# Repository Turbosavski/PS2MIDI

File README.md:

# PS2MIDI

PS/2 protocol and devices as midi interfaces: computer keyboard, mouse, touchpad

KiCad 5.1.5 files are provided for the small pcb board. For now existing / tested as a single sided prototypes for touchpad and computer keyboard. 

Previouly known as AI_SI Touchpad Piano (-> http://www.ljudmila.org/~savskib/?p=979). It is a midi trigger device based on a touchpad system found in any laptop computer – brought to a form of an oversimplified instrument that acts as (ahm...) piano. This module (-> https://www.serdashop.com/waveblaster) replaces the first version with Yamaha XG Midi daughter board (the 90s). My basic interest was just piano sounds.

The heart of the system is (of course) arduino. Arduino Promicro can be set as native usb device – so it was chosen (Sparkfun Pro micro 5V 16MHz version – a Chinese clone). An old laptop (sony vaio) provided a touchpad and parts to make the instrument housing. 

After the touchpad version an old ps/2 computer keyboard was used to some extent with adaptations to the relevant arduino library. Another option is of course the mouse - this would be probably very similar to touchpad. 

All these arduino sketches are available here in their latest development versions:
-> keyboardProMicro04
-> touchPadProMicro14

Quite some work was done in 2019 with adding the AI part on the level of three arduino libraries: midimelodics, midirhythmics and midistatistics - not yet finished but soon to be uploaded. Similar work is lately been done as a flute-like breath controller - but without the midi-synth.

Available here - in case the virus gets me...

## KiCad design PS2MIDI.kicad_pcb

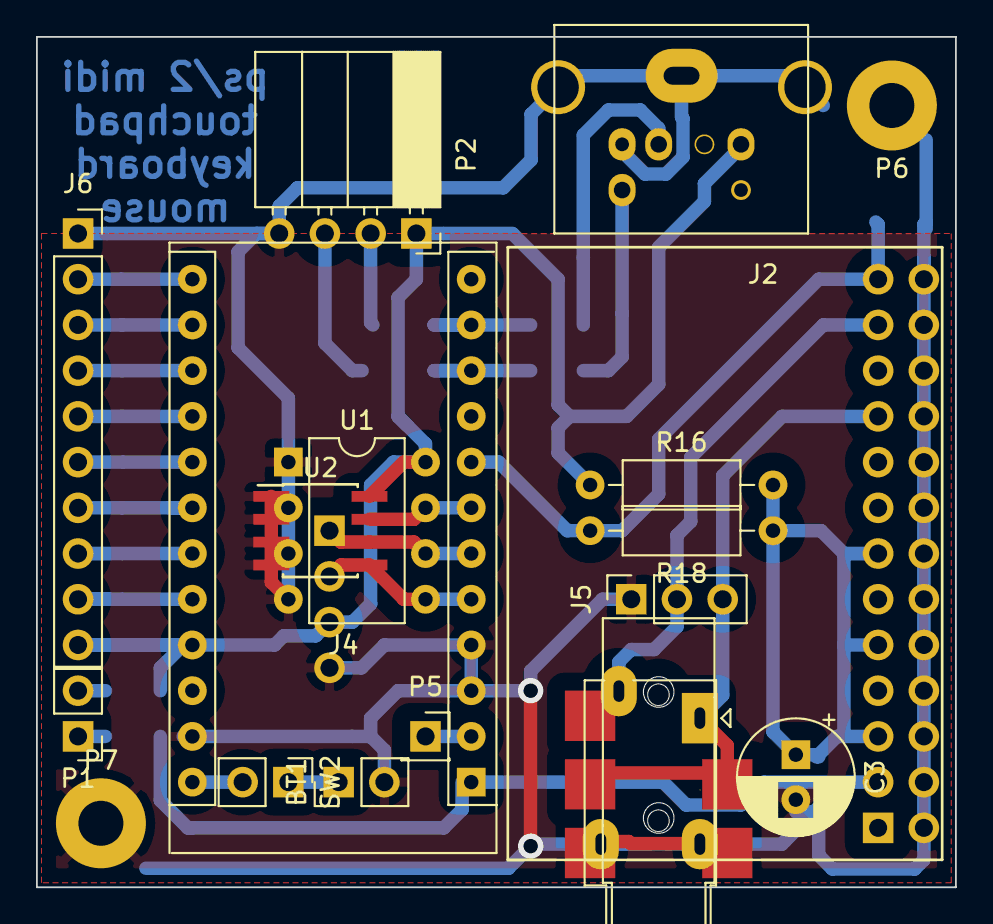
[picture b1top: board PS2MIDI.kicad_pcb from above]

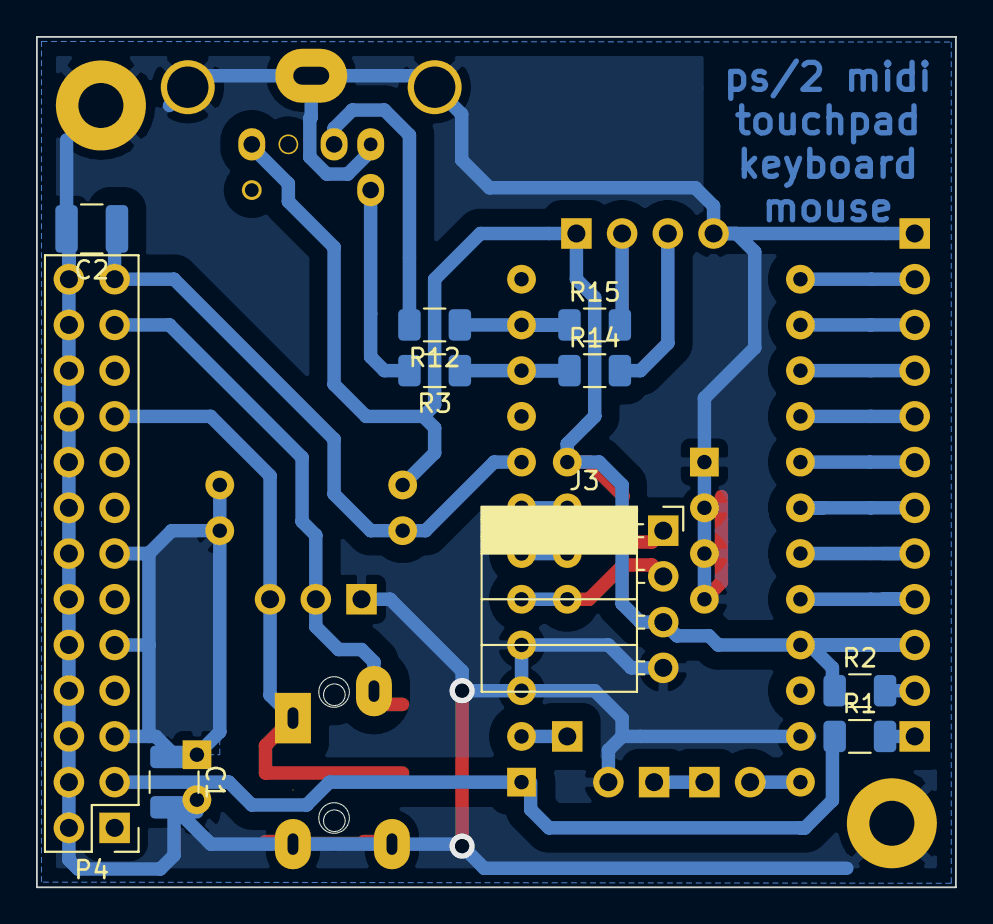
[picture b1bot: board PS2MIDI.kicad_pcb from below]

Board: 2 copper layers, 51.1 x 47.2 mm, 28 parts (10 on the bottom side), 29 nets.

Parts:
BT1: Batt_9V; PinHeader_1x02_P2.54mm_Vertical
C1: 47u; C_1210_3225Metric
C2: 10u; C_1210_3225Metric
C3: 47u; CP_Radial_D6.3mm_P2.50mm
J1: AUDIO_OUT; Jack_3.5mm_Horizontal_THT
J2: PS/2 Mini-DIN-6; MINI_DIN_Horizontal
J3: i2c LCD; PinSocket_1x04_P2.54mm_Horizontal
J4: ARDUINO_PRO_MICRO_SHIELD; Arduino_ProMicro
J5: audio header; PinSocket_1x03_P2.54mm_Vertical
J6: Conn_01x10_Female; PinSocket_1x10_P2.54mm_Vertical
J7: AUDIO_OUT; Jack_3.5mm_SMT_Horizontal
P1: MIDI_OUT; PinHeader_1x02_P2.54mm_Vertical
P2: Touchpad; PinSocket_1x04_P2.54mm_Horizontal
P4: CONN_02X13; PinHeader_2x13_P2.54mm_Vertical
P5: MIDI_IN; PinSocket_1x01_P2.54mm_Vertical
P6, P7: GND; MountingHole_2.5mm_Pad
R1, R2, R3, R12, R14, R15: 220; R_1206_3216Metric
R16: 12; R_Axial_DIN0207_L6.3mm_D2.5mm_P10.16mm_Horizontal
R18: 10K; R_Axial_DIN0207_L6.3mm_D2.5mm_P10.16mm_Horizontal
SW2: ON_OFF; PinHeader_1x02_P2.54mm_Vertical
U1: 24C256; DIP-8_W7.62mm
U2: 24C256; PowerIntegrations_SO-8

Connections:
GND: BT1.2, C1.2, C2.2, C3.2, J1.1, J2.3, J3.4, J4.3, J4.4, J4.23, J5.1, J6.1, J7.1, P2.4, P4.2, P4.4, P4.6, P4.8, P4.10, P4.12, P4.14, P4.16, P4.18, P4.20, P4.22, P4.24, P4.26, U1.1, U1.2, U1.3, U1.4, U2.1, U2.2, U2.3, U2.4
unnamed: BT1.1, SW2.1
unnamed: C1.1, C3.1, P4.5, P4.9, P4.13, R16.2, R18.1
unnamed: C2.1, J4.8, P4.25, R18.2
unnamed: J1.2, J5.3, J7.2, P4.19
unnamed: J1.3, J5.2, J7.3, P4.23
unnamed: J2.1, R12.2
unnamed: J2.4, J3.3, J4.21, J6.10, P2.1, R2.1, R16.1, U1.8, U2.8
unnamed: J2.5, R3.2
unnamed: J3.1, J4.6, U1.6, U2.6
unnamed: J3.2, J4.5, U1.5, U2.5
unnamed: J4.1, P4.3, R1.1
unnamed: J4.2, P5.1
unnamed: J4.7, U1.7, U2.7
unnamed: J4.10, R3.1, R14.1
unnamed: J4.11, R12.1, R15.1
unnamed: J4.13, J6.2
unnamed: J4.14, J6.3
unnamed: J4.15, J6.4
unnamed: J4.16, J6.5
unnamed: J4.17, J6.6
unnamed: J4.18, J6.7
unnamed: J4.19, J6.8
unnamed: J4.20, J6.9
unnamed: J4.24, SW2.2
unnamed: P1.1, R1.2
unnamed: P1.2, R2.2
unnamed: P2.2, R15.2
unnamed: P2.3, R14.2
